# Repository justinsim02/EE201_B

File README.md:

## EE201_B

An exclusively lab-based class focused on basic hands-on skills for electrical and computer engineers. Topics include soldering, PCB layout, basic microcontroller coding, 3D printing, use of basic test and measurement equipment, file management and version control. Prerequisite: CSE 122, CSE 123, CSE 142, or CSE 143, any of which may be taken concurrently

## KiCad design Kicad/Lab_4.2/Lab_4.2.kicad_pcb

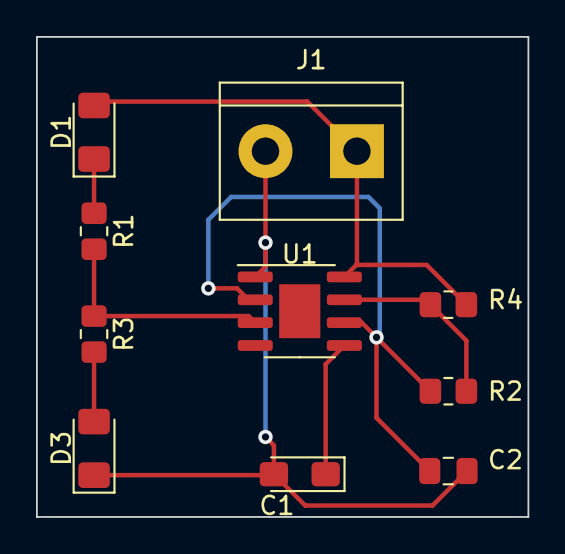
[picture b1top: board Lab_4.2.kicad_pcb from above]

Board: 2 copper layers, 27.3 x 26.7 mm, 10 parts (0 on the bottom side), 8 nets.

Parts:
C1: 0.01 uF; CP_EIA-3216-18_Kemet-A_Pad1.58x1.35mm_HandSolder
C2: 10 uF; C_0805_2012Metric_Pad1.18x1.45mm_HandSolder
D1, D3: LED; LED_1206_3216Metric_Pad1.42x1.75mm_HandSolder
J1: TerminalBlock_bornier-2_P5.08mm
R1, R3, R4: 1K; R_0805_2012Metric_Pad1.20x1.40mm_HandSolder
R2: 10K; R_0805_2012Metric_Pad1.20x1.40mm_HandSolder
U1: 555 Timer; SOIC-8-1EP_3.9x4.9mm_P1.27mm_EP2.29x3mm

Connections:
+9V: D1.2 (A), J1.1, R4.1, U1.8 (VCC)
/pin_2: C2.2, R2.2, U1.2 (TR), U1.6 (THR)
/pin_3: R1.2, R3.1, U1.3 (Q)
GND: C1.2, C2.2, D3.1 (K), J1.2, U1.1 (GND)
unnamed: C1.1, U1.5 (CV)
unnamed: D1.1 (K), R1.1
unnamed: D3.2 (A), R3.2
unnamed: R2.1, R4.2, U1.7 (DIS)

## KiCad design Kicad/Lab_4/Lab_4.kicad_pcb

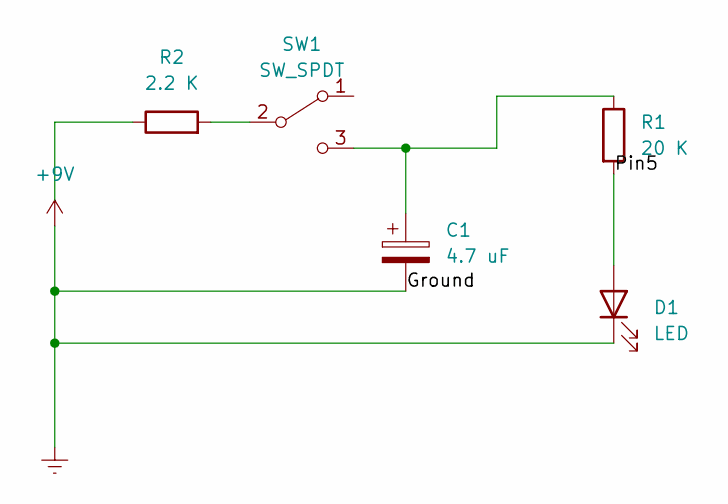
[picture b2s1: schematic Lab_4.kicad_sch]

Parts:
C1: 4.7 uF; C_Radial_D5.0mm_H5.0mm_P2.00mm
D1: LED; LED_D5.0mm
R1: 20 K; R_Axial_DIN0516_L15.5mm_D5.0mm_P20.32mm_Horizontal
R2: 2.2 K; R_Axial_DIN0516_L15.5mm_D5.0mm_P20.32mm_Horizontal
SW1: SW_SPDT; SW_E-Switch_EG1224_SPDT_Angled

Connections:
+9V: C1.2, D1.1 (K)
/Pin5: D1.2 (A), R1.2
unnamed: C1.1, R1.1, SW1.3 (C)
unnamed: R2.2, SW1.2 (B)

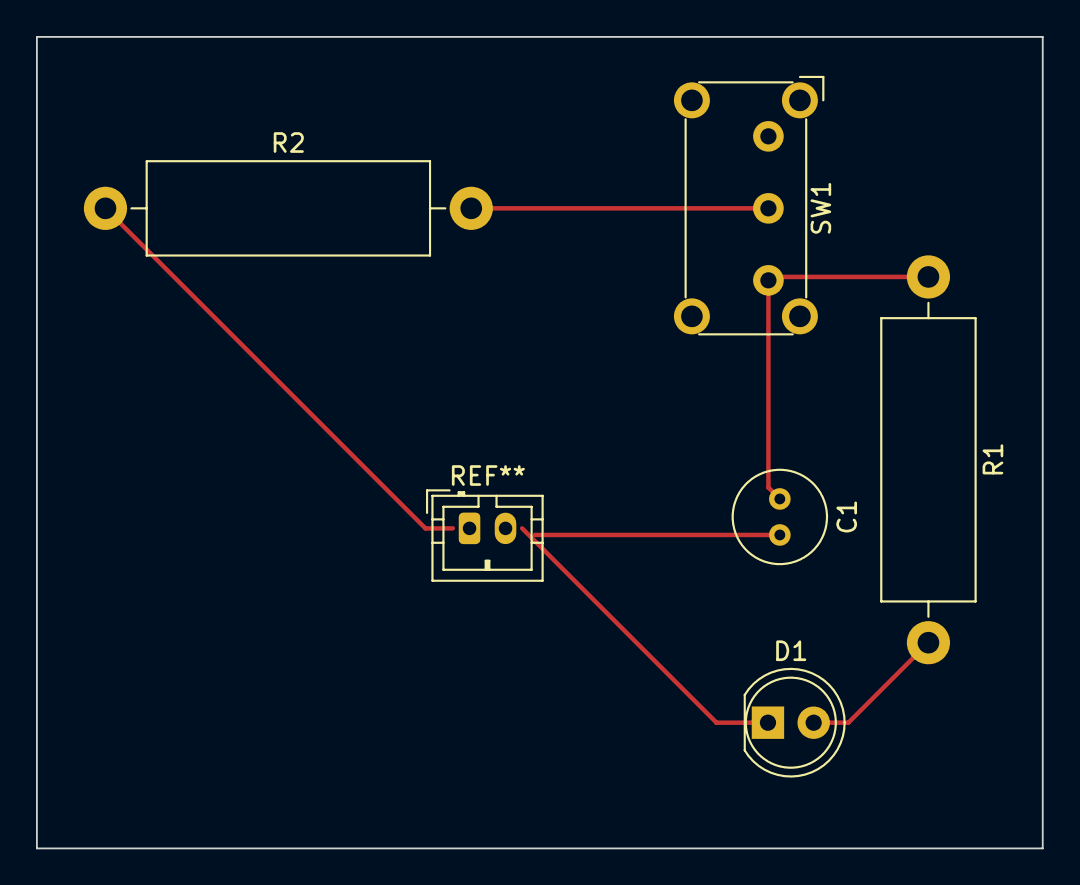
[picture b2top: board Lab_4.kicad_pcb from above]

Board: 2 copper layers, 55.9 x 45.1 mm, 5 parts (0 on the bottom side), 4 nets.

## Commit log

2023-01-13 stuff
2023-01-13 more stuff
2023-01-19 New Arduino branch
2023-01-19 message
2023-01-20 adding Arduino Exercises
2023-01-26 added KiCAD stuff
2023-02-02 New Soldering Branch and photos of Lab 5
2023-02-10 pcb design
2023-02-16 new gerber files for 4.2
2023-03-17 Add files via upload
    pictures of device
